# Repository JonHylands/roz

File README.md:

roz
===

Code repository for Roz, my quad walker robot.

Roz is now controlled by a custom MicroPython board.

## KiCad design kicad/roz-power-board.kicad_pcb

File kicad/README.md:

Rev 0.2 Changes

Schematic
- fixed Q2 (swapped source & drain)
- added P_JUMP to bypass pushbutton SW2
- fixed voltage regulator U1 (swapped in and out)
- added USR_SW
- added BOOT0 connection to PB8

PCB
- corresponding changes from schematic changes
- moved BATT_BALANCE connector for 5 volt regulator screw clearance
- increased size of 5 volt regulator pin holes
- changed C3 to be a slightly larger cap (old one wasn't rated for 12 volts)
- fixed the silkscreen for the Bioloid AX-12 connector

Pins
- GATE_PIN (A14) - Bring GATE_PIN high to keep power going to the MCU, bring GATE_PIN
    low to turn the MCU off. Pressing the PowerSwitch acts as a bootstrap
    to turn power on, and it must remain pressed until the MCU brings
    GATE_PIN high
- SWITCH_PIN (A13) - Allows the MCU to detect when SW2 has been pressed. This is
    typically used as a way of indicating that a shudown should be
    initiated. However, you could also discern between long press and
    short press to perform different things.
- GPIO_A4, GPIO_A5, GPIO_A6, GPIO_A7 - These are 3 pins headers with power,
    ground and signal available. The power signal can be switched between
    3.3v and 5v by using a solder ball. By default power is connected to 3.3v
    but the trace can be cut using an X-Acto knife.
    The signal lines can be configured as digital lines or as ADC lines. As
    digital lines they are 3.3v but 5v tolerant. As ADC, they are limited to
    3.3v
- STAT_PIN (A15) - low when wall adapter is present.
- LED_R (B0/TIM3_CH3), LED_G (B1/TIM3_CH4), LEB_B (B5/TIM3_CH2) - used to
    control the RGB status LED. All 3 LEDs are also connected to TIM3 so you
    can use PWM to control the brightness.
- CELL1_VOLTAGE (A0), CELL2_VOLTAGE (A1), CELL3_VOLTAGE (A3) - connected to
    the battery balance connector. Each signal will read 25% of the real voltage.
    The voltage of each cell can be inferred by subtracting the voltage of the
    earlier cell. This can be used to detect batteries which are not properly
    balanced.
- BIOLOID_TX (A2) - Connects to the bioloid bus.
- VBUS (PA9) - Can be used to detect when the USB cable is plugged in.
- UART1_TX (B6), UART1_RX (B7) - UART port 1. Can be used for debugging or
    connecting a serial based sensor. Can also be used to bootload code.
- I2C2_SDA (B3), I2C_SCL (B10) - I2C bus 2. Can be used to connect additional
    peripherals/sensors.
- SPI2_CS1 (B12), SPI_CS2 (A8), SPI2_MOSI (B15), SPI2_MISO (B14), SPI2_SCK (B13)
    SPI port available for external peripherals/sensors.
- USR_SW (C13) - can be used as a digital I/O pin.
- P_JUMP - can be used to force power on until such time as the MCU does this itself.
- ALT_3.3 - can be used to power the MCU if the 5V regulator is unplugged.
- RPI - 5V power used to provide power to the host processor (RPi)
- BUS_SWITCH - can be connected to a switch to control Bioloid Bus Power.

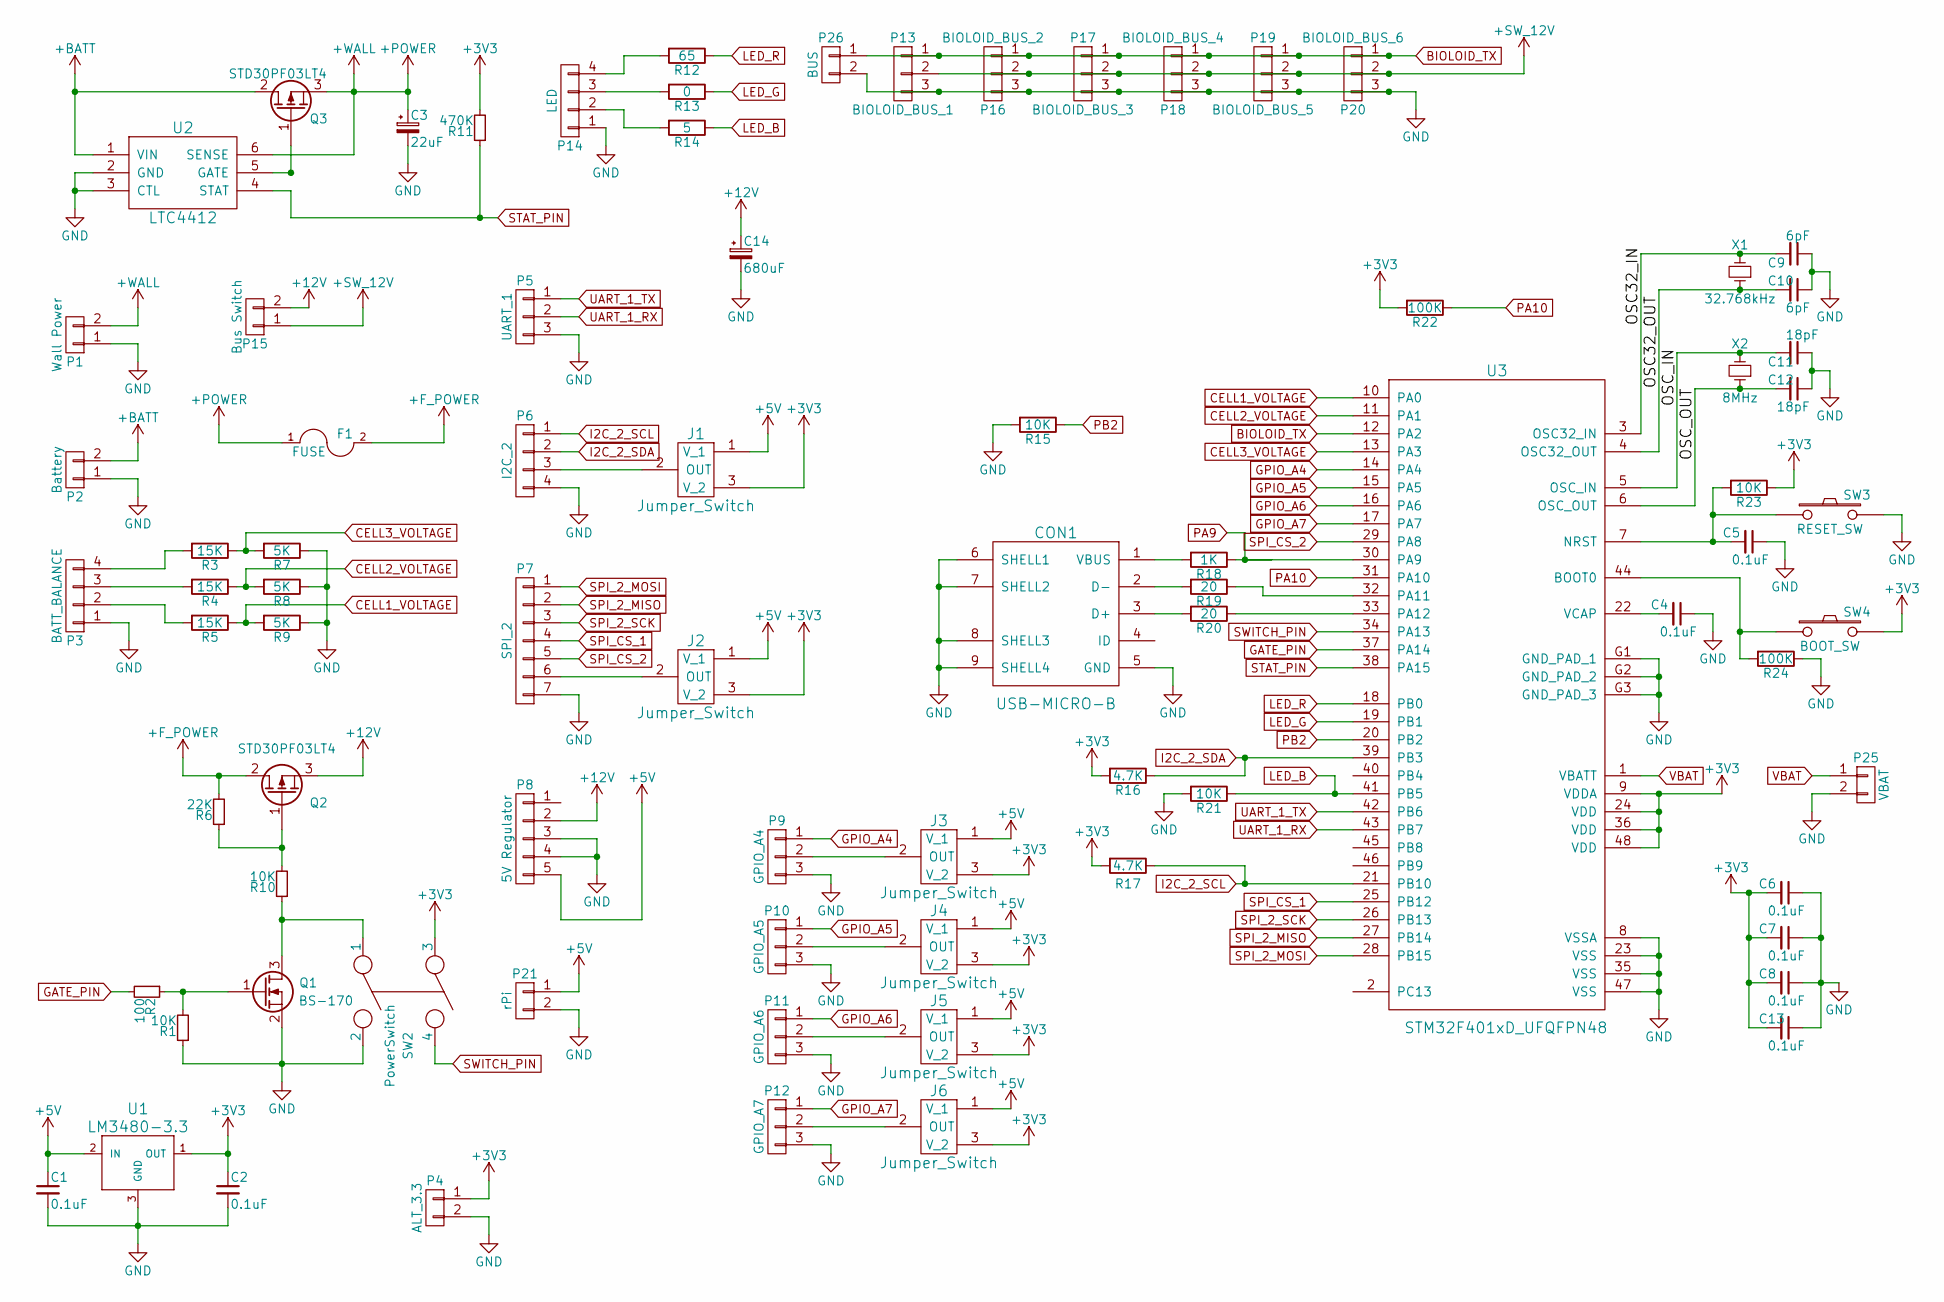
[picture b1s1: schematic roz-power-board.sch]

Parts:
C1, C2, C4, C5, C6, C7, C8, C13: 0.1uF; C_0603
C3: 22uF; c_elec_3x5.3
C9, C10: 6pF; C_0603
C11, C12: 18pF; C_0603
C14: 680uF; C_Radial_D8_L21_P3.8
CON1: USB-MICRO-B; USB_MICRO_B
F1: FUSE; BladeFuse-CarType
J1, J2, J3, J4, J5, J6: Jumper_Switch; Jumper-Switch
P1: Wall Power; TerminalBlock
P2: Battery; TerminalBlock
P3: BATT_BALANCE; Socket_Strip_Straight_1x04
P4: ALT_3.3; SIL_2_050
P5: UART_1; SIL_3_050
P6: I2C_2; SIL_4_050
P7: SPI_2; SIL_7_050
P8: 5V Regulator; 5V_5A_VReg
P9: GPIO_A4; SIL_3_050
P10: GPIO_A5; SIL_3_050
P11: GPIO_A6; SIL_3_050
P12: GPIO_A7; SIL_3_050
P13: BIOLOID_BUS_1; Bioloid-3
P14: LED; SIL_4_050
P15: Bus Switch; TerminalBlock
P16: BIOLOID_BUS_2; Bioloid-3
P17: BIOLOID_BUS_3; Bioloid-3
P18: BIOLOID_BUS_4; Bioloid-3
P19: BIOLOID_BUS_5; Bioloid-3
P20: BIOLOID_BUS_6; Bioloid-3
P21: rPi; SIL_2_050
P25: VBAT; SIL_2_050
P26: BUS; SIL_2_050
Q1: BS-170; SOT-23
Q2, Q3: STD30PF03LT4; TO-252-2Lead
R1, R10, R15, R21, R23: 10K; R_0603
R2: 100; R_0603
R3, R4, R5: 15K; R_0603
R6: 22K; R_0603
R7, R8, R9: 5K; R_0603
R11: 470K; R_0603
R12: 65; R_0603
R13: 0; R_0603
R14: 5; R_0603
R16, R17: 4.7K; R_0603
R18: 1K; R_0603
R19, R20: 20; R_0603
R22, R24: 100K; R_0603
SW2: PowerSwitch; SIL_4_050
SW3: RESET_SW; PUSH_SMT
SW4: BOOT_SW; PUSH_SMT
U1: LM3480-3.3; SOT-23
U2: LTC4412; SOT-23-6
U3: STM32F401xD_UFQFPN48; UFQFPN48
X1: 32.768kHz; CRYSTAL_SMT_3
X2: 8MHz; CRYSTAL_SMT

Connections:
+3V3: C2.1, C6.2, C7.2, C8.2, C13.2, J1.3 (V_2), J2.3 (V_2), J3.3 (V_2), J4.3 (V_2), J5.3 (V_2), J6.3 (V_2), P4.1, R11.2, R16.2, R17.2, R22.2, R23.1, SW2.3, SW4.2, U1.1 (OUT), U3.9 (VDDA), U3.24 (VDD), U3.36 (VDD), U3.48 (VDD)
+5V: C1.1, J1.1 (V_1), J2.1 (V_1), J3.1 (V_1), J4.1 (V_1), J5.1 (V_1), J6.1 (V_1), P8.5, P21.1, U1.2 (IN)
+12V: C14.1, P8.2, P15.2, Q2.3 (S)
+BATT: P2.2, Q3.2 (D), U2.1 (VIN)
+F_POWER: F1.2, Q2.2 (D), R6.2
+POWER: C3.1, F1.1, P1.2, Q3.3 (S), U2.6 (SENSE)
+SW_12V: P13.2, P15.1, P16.2, P17.2, P18.2, P19.2, P20.2
/OSC32_IN: C9.2, U3.3 (OSC32_IN), X1.2
/OSC32_OUT: C10.2, U3.4 (OSC32_OUT), X1.1
/OSC_IN: C11.2, U3.5 (OSC_IN), X2.2
/OSC_OUT: C12.2, U3.6 (OSC_OUT), X2.1
BIOLOID_TX: P13.1, P16.1, P17.1, P18.1, P19.1, P20.1, P26.1, U3.12 (PA2)
CELL1_VOLTAGE: R5.1, R9.2, U3.10 (PA0)
CELL2_VOLTAGE: R4.1, R8.2, U3.11 (PA1)
CELL3_VOLTAGE: R3.1, R7.2, U3.13 (PA3)
GATE_PIN: R2.2, U3.37 (PA14)
GND: C1.2, C2.2, C3.2, C4.1, C5.1, C6.1, C7.1, C8.1, C9.1, C10.1, C11.1, C12.1, C13.1, C14.2, CON1.5 (GND), CON1.6 (SHELL1), CON1.7 (SHELL2), CON1.8 (SHELL3), CON1.9 (SHELL4), P1.1, P2.1, P3.1, P4.2, P5.3, P6.4, P7.7, P8.3, P8.4, P9.3, P10.3, P11.3, P12.3, P13.3, P14.1, P16.3, P17.3, P18.3, P19.3, P20.3, P21.2, P25.2, P26.2, Q1.2 (S), R1.1, R7.1, R8.1, R9.1, R15.2, R21.2, R24.1, SW2.2, SW3.2, U1.3 (GND), U2.2 (GND), U2.3 (CTL), U3.8 (VSSA), U3.23 (VSS), U3.35 (VSS), U3.47 (VSS), U3.G1 (GND_PAD_1), U3.G2 (GND_PAD_2), U3.G3 (GND_PAD_3)
GPIO_A4: P9.1, U3.14 (PA4)
GPIO_A5: P10.1, U3.15 (PA5)
GPIO_A6: P11.1, U3.16 (PA6)
GPIO_A7: P12.1, U3.17 (PA7)
I2C_2_SCL: P6.1, R17.1, U3.21 (PB10)
I2C_2_SDA: P6.2, R16.1, U3.39 (PB3)
LED_B: R14.1, R21.1, U3.41 (PB5)
LED_G: R13.1, U3.19 (PB1)
LED_R: R12.1, U3.18 (PB0)
unnamed: C4.2, U3.22 (VCAP)
unnamed: C5.2, R23.2, SW3.1, U3.7 (NRST)
unnamed: CON1.1 (VBUS), R18.2
unnamed: CON1.2 (D-), R19.2
unnamed: CON1.3 (D+), R20.2
unnamed: J1.2 (OUT), P6.3
unnamed: J2.2 (OUT), P7.6
unnamed: J3.2 (OUT), P9.2
unnamed: J4.2 (OUT), P10.2
unnamed: J5.2 (OUT), P11.2
unnamed: J6.2 (OUT), P12.2
unnamed: P3.2, R5.2
unnamed: P3.3, R4.2
unnamed: P3.4, R3.2
unnamed: P14.2, R14.2
unnamed: P14.3, R13.2
unnamed: P14.4, R12.2
unnamed: Q1.1 (G), R1.2, R2.1
unnamed: Q1.3 (D), R10.1, SW2.1
unnamed: Q2.1 (G), R6.1, R10.2
unnamed: Q3.1 (G), U2.5 (GATE)
unnamed: R19.1, U3.32 (PA11)
unnamed: R20.1, U3.33 (PA12)
unnamed: R24.2, SW4.1, U3.44 (BOOT0)
PA9: R18.1, U3.30 (PA9)
PA10: R22.1, U3.31 (PA10)
PB2: R15.1, U3.20 (PB2)
SPI_2_MISO: P7.2, U3.27 (PB14)
SPI_2_MOSI: P7.1, U3.28 (PB15)
SPI_2_SCK: P7.3, U3.26 (PB13)
SPI_CS_1: P7.4, U3.25 (PB12)
SPI_CS_2: P7.5, U3.29 (PA8)
STAT_PIN: R11.1, U2.4 (STAT), U3.38 (PA15)
SWITCH_PIN: SW2.4, U3.34 (PA13)
UART_1_RX: P5.2, U3.43 (PB7)
UART_1_TX: P5.1, U3.42 (PB6)
VBAT: P25.1, U3.1 (VBATT)

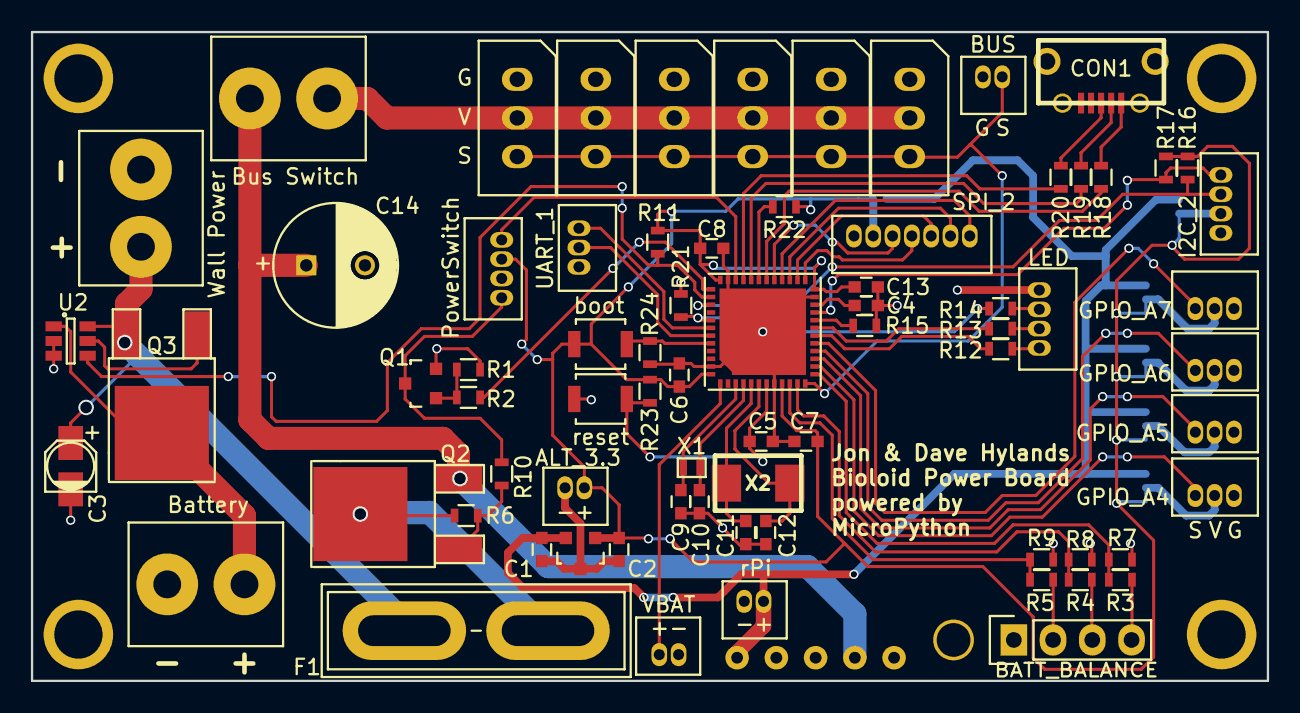
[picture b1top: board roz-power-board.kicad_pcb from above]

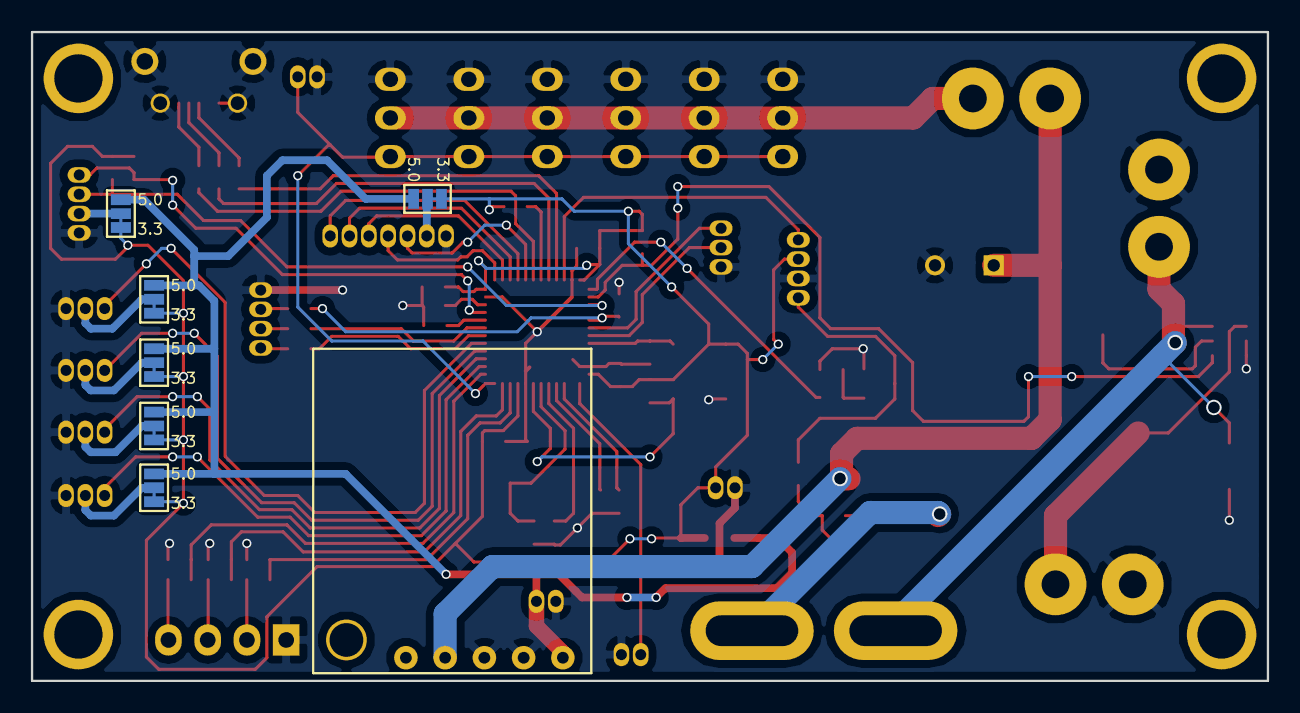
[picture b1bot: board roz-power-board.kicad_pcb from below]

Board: 2 copper layers, 80.0 x 42.0 mm, 85 parts (7 on the bottom side), 63 nets.

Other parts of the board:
1PIN, 1PIN#2, 1PIN#3, 1PIN#4: P***; 4_40_hole
1PIN#5: P***; 2_56_hole

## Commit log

2013-12-10 First cut of code, full IK walking, amble gait, simple FSM with obstacle avoidance
2013-12-15 Minor stylistic fixes
2013-12-25 Separated IK Engine from main module
2013-12-26 First cut of RobotMonitor GUI
2013-12-26 Working monitor GUI, no real data feed yet
2013-12-26 Used smaller images, monitoring frame rate now
2013-12-26 Cached pitch & roll images
2013-12-26 Fixed roz to read range sensors in one shot
2013-12-27 Added timebase to FSM, added heartbeat state machine, plus general writeData function in BioloidController
2013-12-27 Added watchdog state machine to handle low voltage check
2013-12-27 Refactor, plus added temperature check to servos
2015-11-28 Changed Roz to use MicroPython - basic walking code working now
2015-11-29 fixed comment picture link
2015-11-30 Changed to use GP2D12 range sensors, updated range finder formula accordingly
2015-11-30 General re-org, better head positioning at start
2015-11-30 bunch of small changes, experimentation
2015-12-01 minor changes & fixes
2015-12-01 changed obstacle avoidance, slight refactor of controller
2015-12-02 lots of rework, refactoring, cleanup
2015-12-02 added obstacle scanning
2015-12-03 working on various bits & pieces
2015-12-14 Lots of updates to RobotSupport (new system)
2015-12-15 fixes
2015-12-15 other changes
2015-12-17 added pre-init of all leg servos
2015-12-22 Created ObjectExplorer
2015-12-22 added support for dictionaries
2016-01-02 new power board
2016-01-03 more fixes to power board pcb
2016-01-03 more cleanup, changes
2016-01-03 fixed power switch to match netlist/schematic
2016-01-03 Final cleanup/adjustments
2016-01-23 rev 0.2 of the power board
2016-01-23 added list of changes for rev 0.2
2016-10-08 Misc updates
2016-11-06 Added documentation for various pins
2017-01-05 Fixed a typo
